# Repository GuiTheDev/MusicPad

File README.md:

# MusicPad🔧🎶

Schematic:

PCB Design:

**MusicPad** is a small, open-hardware music controller project. It's a compact thingy intended to control music(spotify, youtube and such). This repository contains the PCB design, 3D case model, and firmware.

---

## Project Overview

- **Where the stuff is**
  - PCB design files (`PCB/` KiCad files)
  - 3D model / assembly file for the case (`CAD/MusicPadAss.step`)
  - Firmware prototype (`Firmware/main.py`)

---

## Firmware status 

**The firmware is not finished.** I plan to continue and complete the firmware once I have the hardware in hand to test and iterate on behavior with the real device.(Its just the basic tutorial code!)

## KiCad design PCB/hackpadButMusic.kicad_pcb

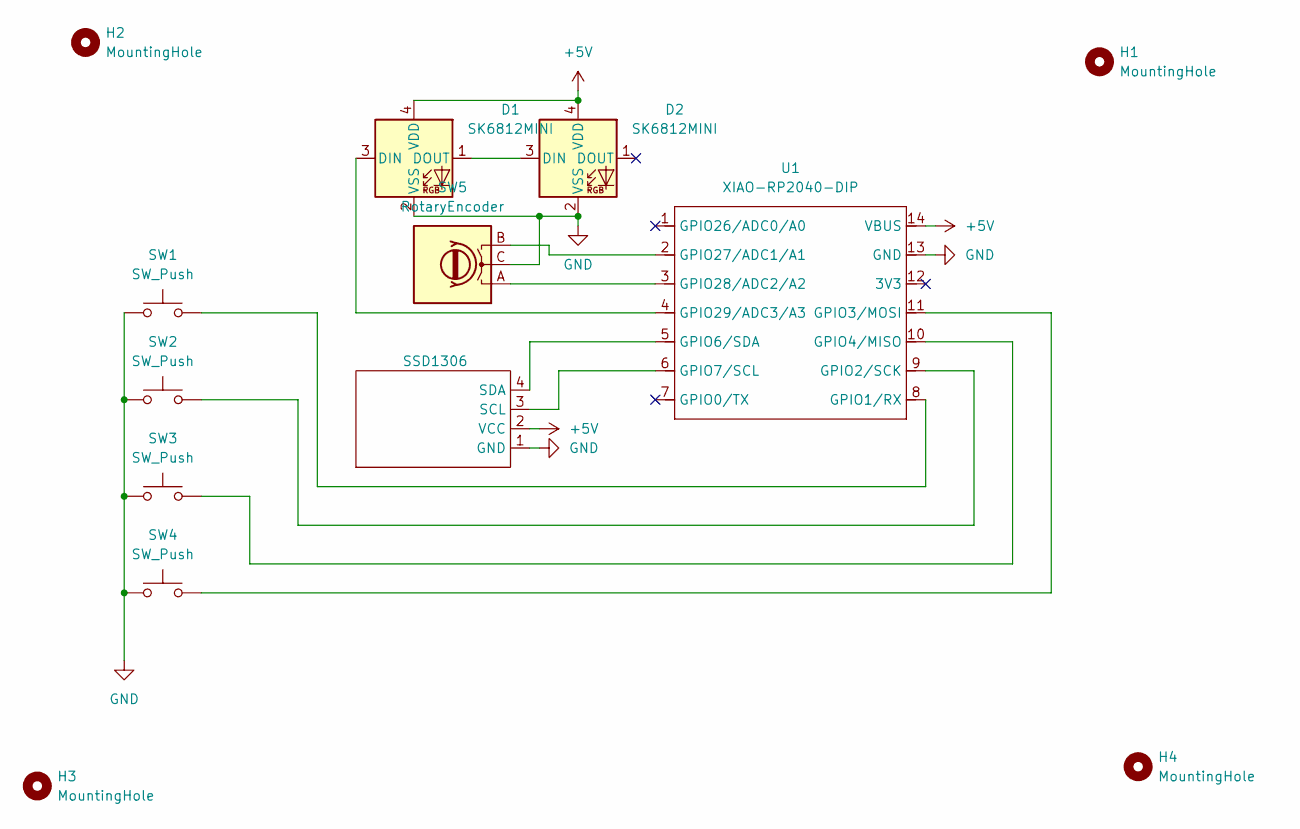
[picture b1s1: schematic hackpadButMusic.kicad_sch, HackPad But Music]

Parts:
D1, D2: SK6812MINI; LED_SK6812MINI_PLCC4_3.5x3.5mm_P1.75mm
H1, H2, H3, H4: MountingHole; MountingHole_3.2mm_M3_Pad
SSD1306: SSD1306_IDINTSEE
SW1, SW2, SW3, SW4: SW_Push; SW_Cherry_MX_1.00u_PCB
SW5: RotaryEncoder; RotaryEncoder_Alps_EC12E_Vertical_H20mm_CircularMountingHol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
U1: XIAO-RP2040-DIP

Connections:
+5V: D1.4 (VDD), D2.4 (VDD), SSD1306.2 (VCC), U1.14 (VBUS)
GND: D1.2 (VSS), D2.2 (VSS), SSD1306.1 (GND), SW1.1, SW2.1, SW3.1, SW4.1, SW5.C, U1.13 (GND)
unnamed: D1.3 (DIN), U1.4 (GPIO29/ADC3/A3)
unnamed: D1.1 (DOUT), D2.3 (DIN)
unnamed: SSD1306.3 (SCL), U1.6 (GPIO7/SCL)
unnamed: SSD1306.4 (SDA), U1.5 (GPIO6/SDA)
unnamed: SW1.2, U1.8 (GPIO1/RX)
unnamed: SW2.2, U1.9 (GPIO2/SCK)
unnamed: SW4.2, U1.11 (GPIO3/MOSI)
unnamed: SW3.2, U1.10 (GPIO4/MISO)
unnamed: SW5.B, U1.2 (GPIO27/ADC1/A1)
unnamed: SW5.A, U1.3 (GPIO28/ADC2/A2)

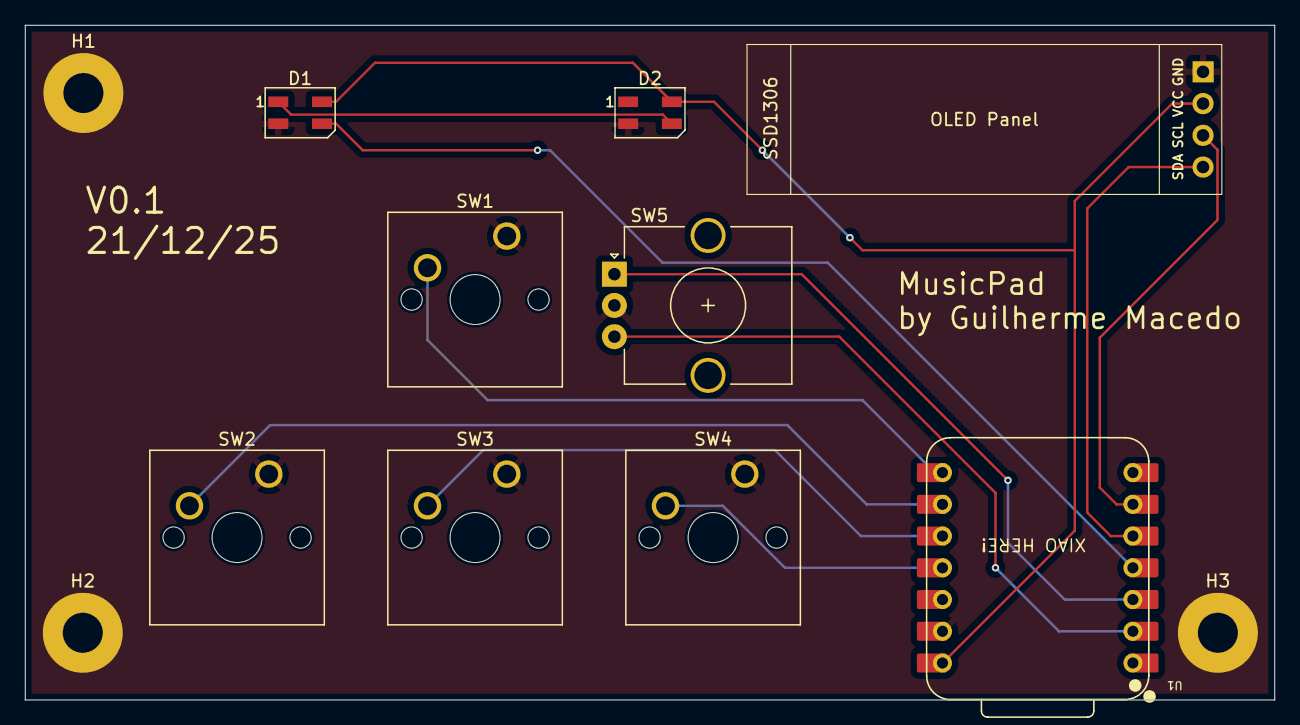
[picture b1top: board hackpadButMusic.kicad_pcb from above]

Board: 2 copper layers, 100.0 x 54.0 mm, 12 parts (0 on the bottom side), 12 nets.

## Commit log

2025-12-22 first commit :)
2025-12-22 Add assembly as .stp
2025-12-22 Some images
2025-12-26 Add image to README.md
    Add image to README for visual representation
2025-12-26 Fix image link in README.md
    Updated image link in README to use raw GitHub URL.
2025-12-27 Update README with schematic and PCB design
    Added schematic and PCB design images to README.
2025-12-27 Revise README for clarity and conciseness
    Updated project description and sections for clarity.
2025-12-27 Update 3D model file format in README
